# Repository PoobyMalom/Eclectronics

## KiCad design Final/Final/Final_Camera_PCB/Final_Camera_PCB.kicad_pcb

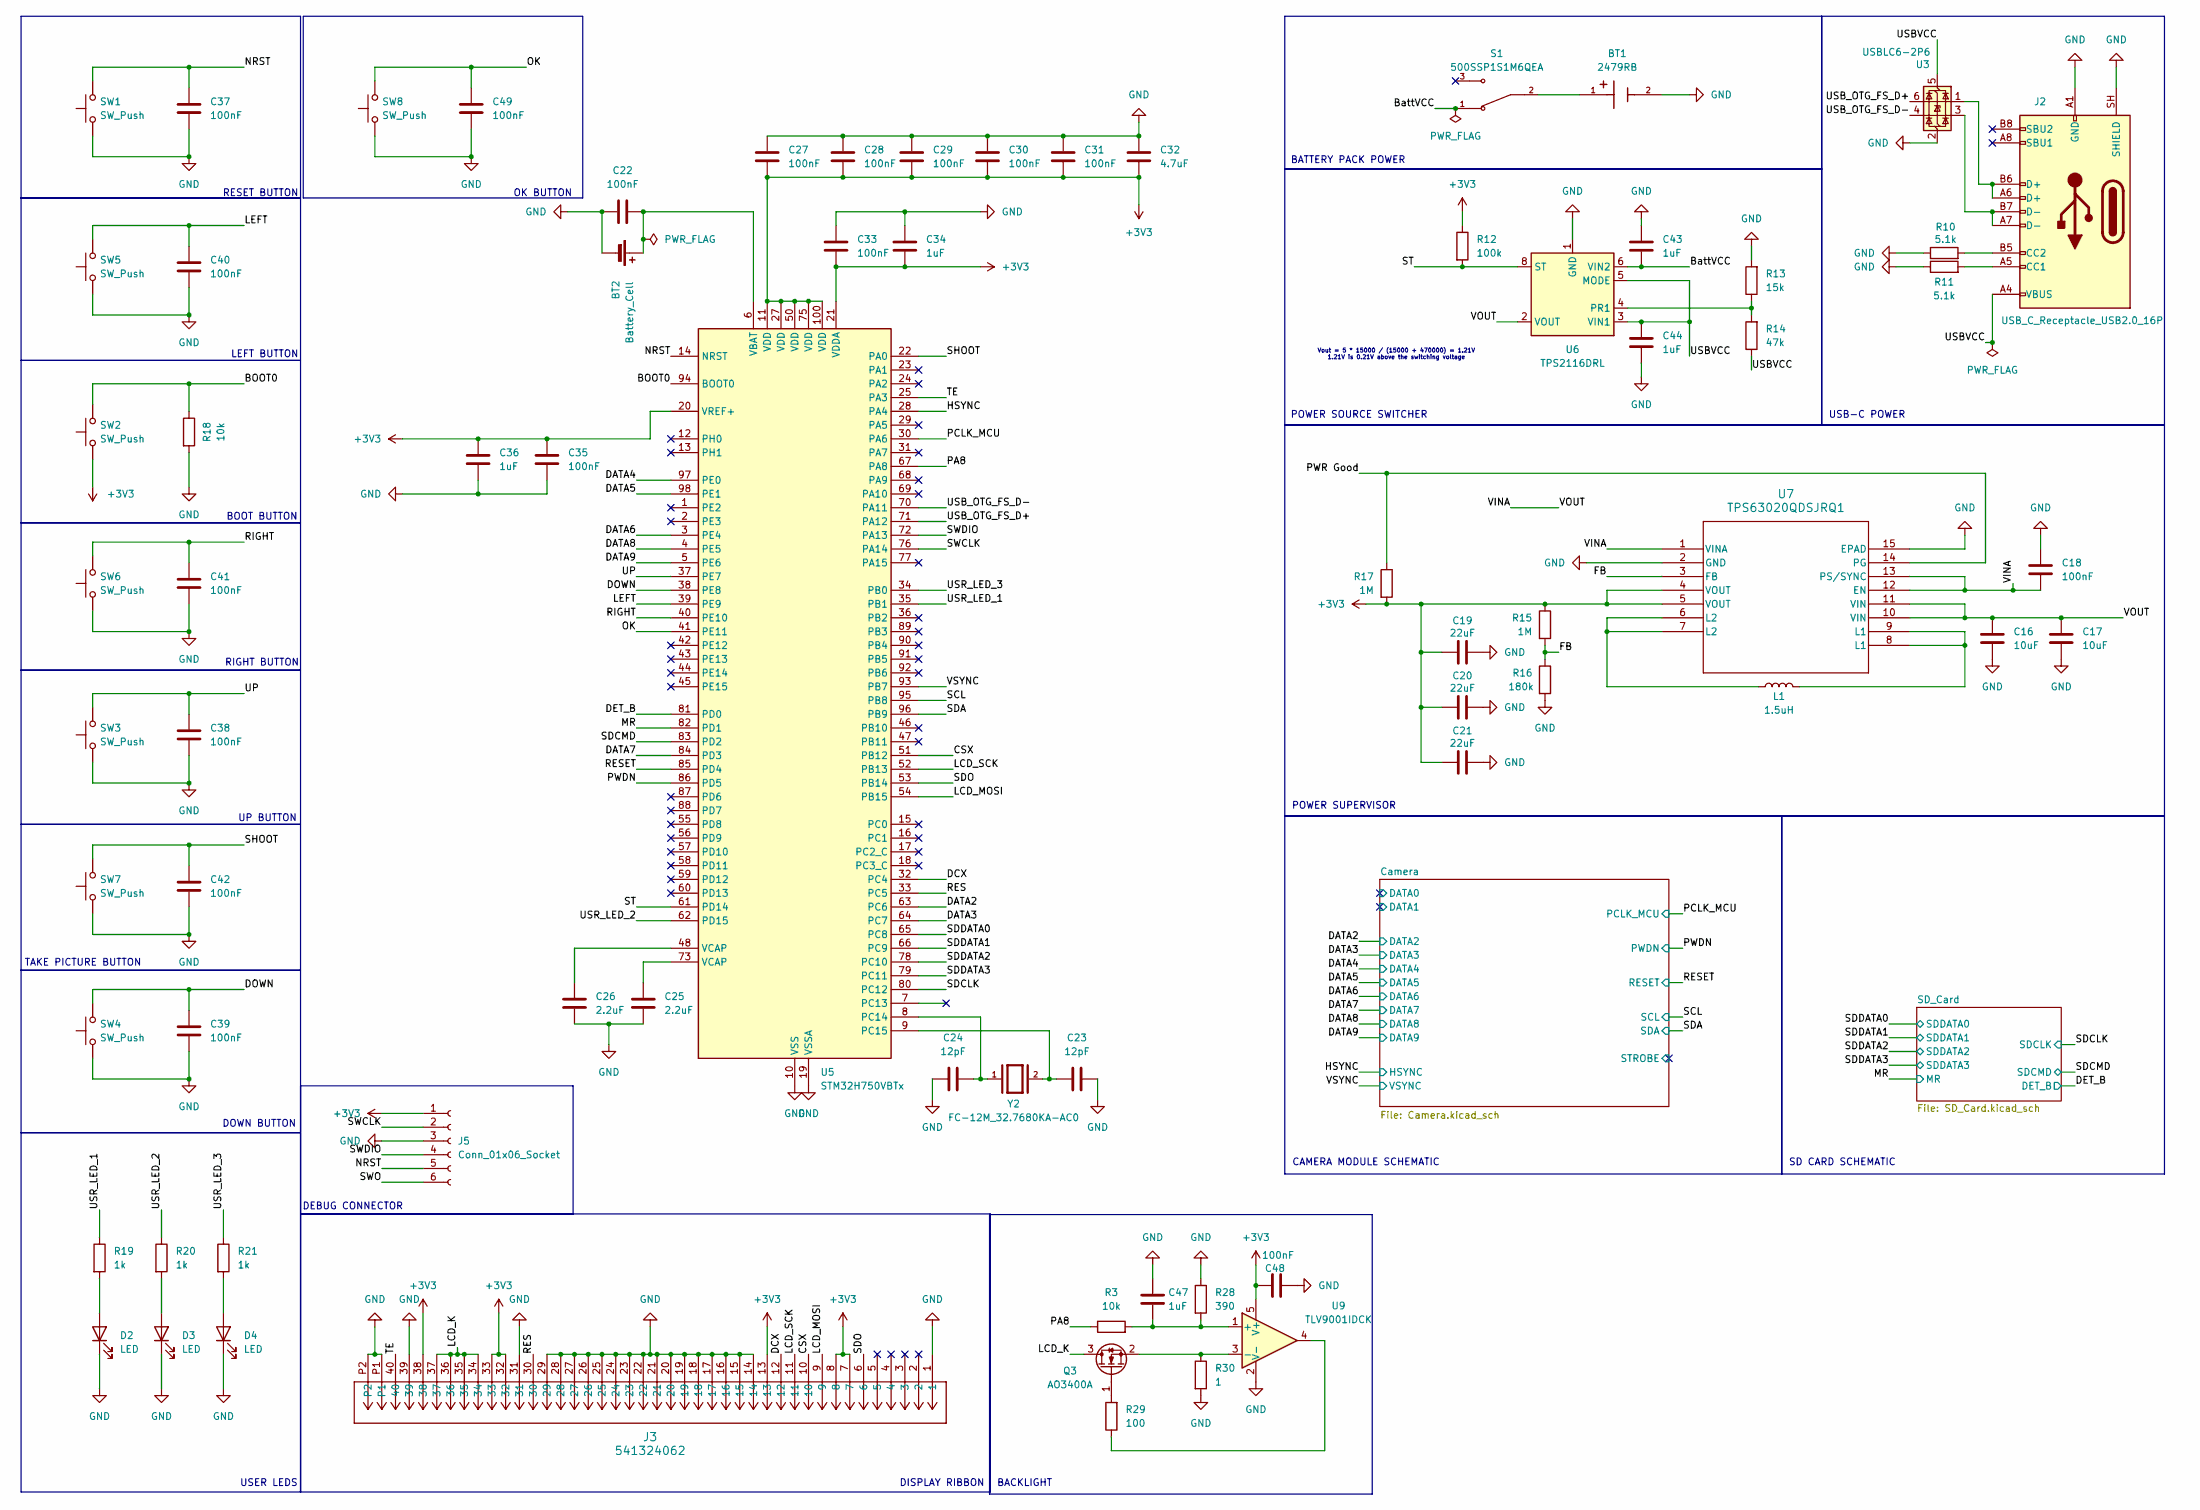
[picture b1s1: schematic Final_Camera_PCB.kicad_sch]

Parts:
BT1: 2479RB; 2479PCB_37P49X52P63_KEY; PARTREV E; DigiKey_Part_Number 36-2479RB-ND
BT2: Battery_Cell; BatteryHolder_Keystone_1060_1x2032
C16, C17: 10uF; C_0805_2012Metric
C18, C22, C27, C28, C29, C30, C31, C33, C35, C37, C38, C39, C40, C41, C42, C48, C49: 100nF; C_0402_1005Metric
C19, C20, C21: 22uF; C_1206_3216Metric
C23, C24: 12pF; C_0402_1005Metric
C25, C26: 2.2uF; C_0603_1608Metric
C32: 4.7uF; C_0603_1608Metric
C34, C36, C43, C44, C47: 1uF; C_0603_1608Metric
D2, D3, D4: LED; LED_0603_1608Metric
J2: USB_C_Receptacle_USB2.0_16P; USB_C_Receptacle_GCT_USB4105-xx-A_16P_TopMnt_Horizontal
J3: 541324062; CON_541324062_MOL
J5: Conn_01x06_Socket; PinHeader_1x06_P2.54mm_Vertical
L1: 1.5uH; L_1008_2520Metric
Q3: AO3400A; SOT-23
R3, R18: 10k; R_0402_1005Metric
R10, R11: 5.1k; R_0402_1005Metric
R12: 100k; R_0402_1005Metric
R13: 15k; R_0402_1005Metric
R14: 47k; R_0402_1005Metric
R15, R17: 1M; R_0402_1005Metric
R16: 180k; R_0402_1005Metric
R19, R20, R21: 1k; R_0402_1005Metric
R28: 390; R_0402_1005Metric
R29: 100; R_0402_1005Metric
R30: 1; R_0603_1608Metric
S1: 500SSP1S1M6QEA; SW_500SSP1S1M6QEA; PARTREV D
SW1, SW2, SW3, SW4, SW5, SW6, SW7, SW8: SW_Push; SW_SPST_B3U-1000P
U3: USBLC6-2P6; SOT-666
U5: STM32H750VBTx; LQFP-100_14x14mm_P0.5mm
U6: TPS2116DRL; SOT-583-8
U7: TPS63020QDSJRQ1; DSJ14_2P85X1P58
U9: TLV9001IDCK; SOT-353_SC-70-5
Y2: FC-12M_32.7680KA-AC0; XTAL_FC-12M_32.7680KA-AC0; MPN FC-12M 32.7680KA-AC0

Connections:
+3V3: C19.2, C20.2, C21.2, C27.2, C28.2, C29.2, C30.2, C31.2, C32.2, C33.2, C34.2, C35.2, C36.2, C48.1, J3.7, J3.8, J3.13, J3.32, J3.33, J3.38, J5.1, R12.1, R15.1, R17.2, SW2.1, U5.11 (VDD), U5.20 (VREF+), U5.21 (VDDA), U5.27 (VDD), U5.50 (VDD), U5.75 (VDD), U5.100 (VDD), U7.4 (VOUT), U7.5 (VOUT), U9.5 (V+); also elsewhere on the board
/BOOT0: R18.1, SW2.2, U5.94 (BOOT0)
/BattVCC: C43.2, S1.1, U6.6 (VIN2)
/CSX: J3.10, U5.51 (PB12)
/DATA2: U5.63 (PC6); also elsewhere on the board
/DATA3: U5.64 (PC7); also elsewhere on the board
/DATA4: U5.97 (PE0); also elsewhere on the board
/DATA5: U5.98 (PE1); also elsewhere on the board
/DATA6: U5.3 (PE4); also elsewhere on the board
/DATA7: U5.84 (PD3); also elsewhere on the board
/DATA8: U5.4 (PE5); also elsewhere on the board
/DATA9: U5.5 (PE6); also elsewhere on the board
/DCX: J3.12, U5.32 (PC4)
/DET_B: U5.81 (PD0); also elsewhere on the board
/DOWN: C39.1, SW4.2, U5.38 (PE8)
/FB: R15.2, R16.1, U7.3 (FB)
/HSYNC: U5.28 (PA4); also elsewhere on the board
/LCD_K: J3.34, J3.35, J3.36, J3.37, Q3.3 (D)
/LCD_MOSI: J3.9, U5.54 (PB15)
/LCD_SCK: J3.11, U5.52 (PB13)
/LEFT: C40.1, SW5.2, U5.39 (PE9)
/MR: U5.82 (PD1); also elsewhere on the board
/NRST: C37.1, J5.5, SW1.2, U5.14 (NRST)
/OK: C49.1, SW8.2, U5.41 (PE11)
/PA8: R3.1, U5.67 (PA8)
/PCLK_MCU: U5.30 (PA6); also elsewhere on the board
/PWDN: U5.86 (PD5); also elsewhere on the board
/PWR Good: R17.1, U7.14 (PG)
/RES: J3.30, U5.33 (PC5)
/RESET: U5.85 (PD4); also elsewhere on the board
/RIGHT: C41.1, SW6.2, U5.40 (PE10)
/SCL: U5.95 (PB8); also elsewhere on the board
/SDA: U5.96 (PB9); also elsewhere on the board
/SDCLK: U5.80 (PC12); also elsewhere on the board
/SDCMD: U5.83 (PD2); also elsewhere on the board
/SDDATA0: U5.65 (PC8); also elsewhere on the board
/SDDATA1: U5.66 (PC9); also elsewhere on the board
/SDDATA2: U5.78 (PC10); also elsewhere on the board
/SDDATA3: U5.79 (PC11); also elsewhere on the board
/SDO: J3.6, U5.53 (PB14)
/SHOOT: C42.1, SW7.2, U5.22 (PA0)
/ST: R12.2, U5.61 (PD14), U6.8 (ST)
/SWCLK: J5.2, U5.76 (PA14)
/SWDIO: J5.4, U5.72 (PA13)
/SWO: J5.6
/TE: J3.40, U5.25 (PA3)
/UP: C38.1, SW3.2, U5.37 (PE7)
/USBVCC: C44.1, J2.A4 (VBUS), J2.A9 (VBUS), J2.B4 (VBUS), J2.B9 (VBUS), R14.1, U3.5 (VBUS), U6.3 (VIN1), U6.5 (MODE)
/USB_OTG_FS_D+: U3.6 (I/O1), U5.71 (PA12)
/USB_OTG_FS_D-: U3.4 (I/O2), U5.70 (PA11)
/USR_LED_1: R19.1, U5.35 (PB1)
/USR_LED_2: R20.1, U5.62 (PD15)
/USR_LED_3: R21.1, U5.34 (PB0)
/VINA: C16.1, C17.1, C18.1, U6.2 (VOUT), U6.7 (VOUT), U7.1 (VINA), U7.10 (VIN), U7.11 (VIN), U7.12 (EN), U7.13 (PS/SYNC)
/VSYNC: U5.93 (PB7); also elsewhere on the board
GND: BT1.2, BT2.2 (-), C16.2, C17.2, C18.2, C19.1, C20.1, C21.1, C22.2, C23.1, C24.1, C25.2, C26.2, C27.1, C28.1, C29.1, C30.1, C31.1, C32.1, C33.1, C34.1, C35.1, C36.1, C37.2, C38.2, C39.2, C40.2, C41.2, C42.2, C43.1, C44.2, C47.1, C48.2, C49.2, D2.1 (K), D3.1 (K), D4.1 (K), J2.A1 (GND), J2.A12 (GND), J2.B1 (GND), J2.B12 (GND), J2.SH (SHIELD), J3.1, J3.14, J3.15, J3.16, J3.17, J3.18, J3.19, J3.20, J3.21, J3.22, J3.23, J3.24, J3.25, J3.26, J3.27, J3.28, J3.29, J3.31, J3.39, J3.P1, J3.P2, J5.3, R10.1, R11.1, R13.2, R16.2, R18.2, R28.1, R30.2, SW1.1, SW3.1, SW4.1, SW5.1, SW6.1, SW7.1, SW8.1, U3.2 (GND), U5.10 (VSS), U5.19 (VSSA), U5.26 (VSS), U5.49 (VSS), U5.74 (VSS), U5.99 (VSS), U6.1 (GND), U7.2 (GND), U7.15 (EPAD), U9.2 (V-); also elsewhere on the board
unnamed: BT1.1, S1.2
unnamed: BT2.1 (+), C22.1, U5.6 (VBAT)
unnamed: C25.1, U5.73 (VCAP)
unnamed: C26.1, U5.48 (VCAP)
unnamed: D2.2 (A), R19.2
unnamed: D3.2 (A), R20.2
unnamed: D4.2 (A), R21.2
unnamed: J2.A5 (CC1), R11.2
unnamed: J2.B5 (CC2), R10.2
unnamed: J2.A6 (D+), J2.B6 (D+), U3.1 (I/O1)
unnamed: J2.A7 (D-), J2.B7 (D-), U3.3 (I/O2)
unnamed: L1.1, U7.6 (L2), U7.7 (L2)
unnamed: L1.2, U7.8 (L1), U7.9 (L1)
unnamed: Q3.1 (G), R29.2
unnamed: Q3.2 (S), R30.1, U9.3 (-)
unnamed: R29.1, U9.4
unnamed: C24.2, U5.8 (PC14), Y2.1
unnamed: C23.2, U5.9 (PC15), Y2.2
unnamed: R13.1, R14.2, U6.4 (PR1)
unnamed: C47.2, R3.2, R28.2, U9.1 (+)

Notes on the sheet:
BOOT BUTTON
USER LEDS
DOWN BUTTON
SD CARD SCHEMATIC
OK BUTTON
RIGHT BUTTON
USB-C POWER
Vout = 5 * 15000 / (15000 + 470000) = 1.21V 1.21V is 0.21V above the switching voltage
LEFT BUTTON
DISPLAY RIBBON
UP BUTTON
RESET BUTTON
BATTERY PACK POWER
TAKE PICTURE BUTTON
POWER SUPERVISOR
CAMERA MODULE SCHEMATIC
DEBUG CONNECTOR
POWER SOURCE SWITCHER
BACKLIGHT

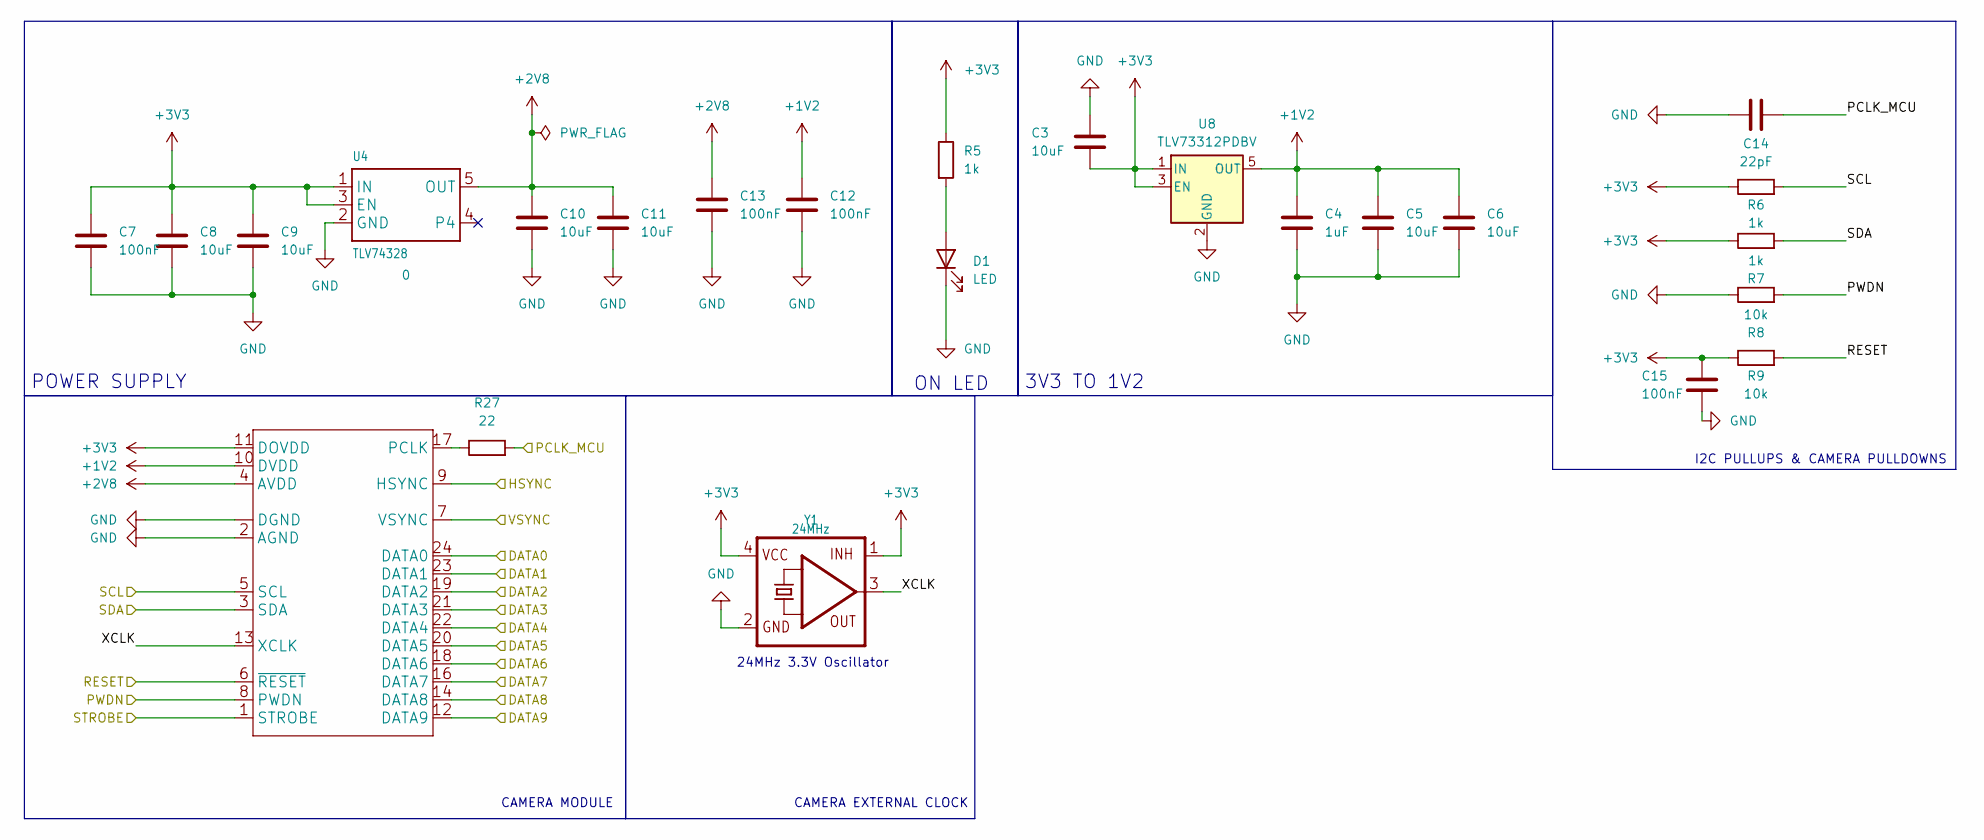
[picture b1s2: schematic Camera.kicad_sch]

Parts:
C3, C5, C6, C8, C9, C10, C11: 10uF; C_0805_2012Metric
C4: 1uF; C_0603_1608Metric
C7, C12, C13, C15: 100nF; C_0402_1005Metric
C14: 22pF; C_0402_1005Metric
D1: LED; LED_0603_1608Metric
R5, R6, R7: 1k; R_0402_1005Metric
R8, R9: 10k; R_0402_1005Metric
R27: 22; R_0402_1005Metric
U4: TLV74328; DBV0005A_N; JLC_ROTATION 270
U8: TLV73312PDBV; SOT-23-5
X1: OV2640FSL
Y1: 24MHz; Oscillator_SMD_Abracon_ASE-4Pin_3.2x2.5mm_HandSoldering

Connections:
+1V2: C4.1, C5.1, C6.1, C12.1, U8.5 (OUT), X1.10 (DVDD)
+2V8: C10.1, C11.1, C13.1, U4.5 (OUT), X1.4 (AVDD)
+3V3: C3.2, C7.1, C8.1, C9.1, C15.2, R5.1, R6.1, R7.1, R9.1, U4.1 (IN), U4.3 (EN), U8.1 (IN), U8.3 (EN), X1.11 (DOVDD), Y1.1 (INH), Y1.4 (VCC); also elsewhere on the board
/Camera/DATA0: X1.24 (DATA0)
/Camera/DATA1: X1.23 (DATA1)
/Camera/STROBE: X1.1 (STROBE)
/Camera/XCLK: X1.13 (XCLK), Y1.3 (OUT)
/DATA2: X1.19 (DATA2); also elsewhere on the board
/DATA3: X1.21 (DATA3); also elsewhere on the board
/DATA4: X1.22 (DATA4); also elsewhere on the board
/DATA5: X1.20 (DATA5); also elsewhere on the board
/DATA6: X1.18 (DATA6); also elsewhere on the board
/DATA7: X1.16 (DATA7); also elsewhere on the board
/DATA8: X1.14 (DATA8); also elsewhere on the board
/DATA9: X1.12 (DATA9); also elsewhere on the board
/HSYNC: X1.9 (HSYNC); also elsewhere on the board
/PCLK_MCU: C14.1, R27.2; also elsewhere on the board
/PWDN: R8.2, X1.8 (PWDN); also elsewhere on the board
/RESET: R9.2, X1.6 (~RESET); also elsewhere on the board
/SCL: R6.2, X1.5 (SCL); also elsewhere on the board
/SDA: R7.2, X1.3 (SDA); also elsewhere on the board
/VSYNC: X1.7 (VSYNC); also elsewhere on the board
GND: C3.1, C4.2, C5.2, C6.2, C7.2, C8.2, C9.2, C10.2, C11.2, C12.2, C13.2, C14.2, C15.1, D1.1 (K), R8.1, U4.2 (GND), U8.2 (GND), X1.2 (AGND), X1.15 (DGND), X1.SPRT1 (DGND), X1.SPRT2 (DGND), Y1.2 (GND); also elsewhere on the board
unnamed: D1.2 (A), R5.2
unnamed: R27.1, X1.17 (PCLK)

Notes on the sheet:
24MHz 3.3V Oscillator
3V3 TO 1V2
I2C PULLUPS & CAMERA PULLDOWNS
CAMERA EXTERNAL CLOCK
CAMERA MODULE
POWER SUPPLY
ON LED

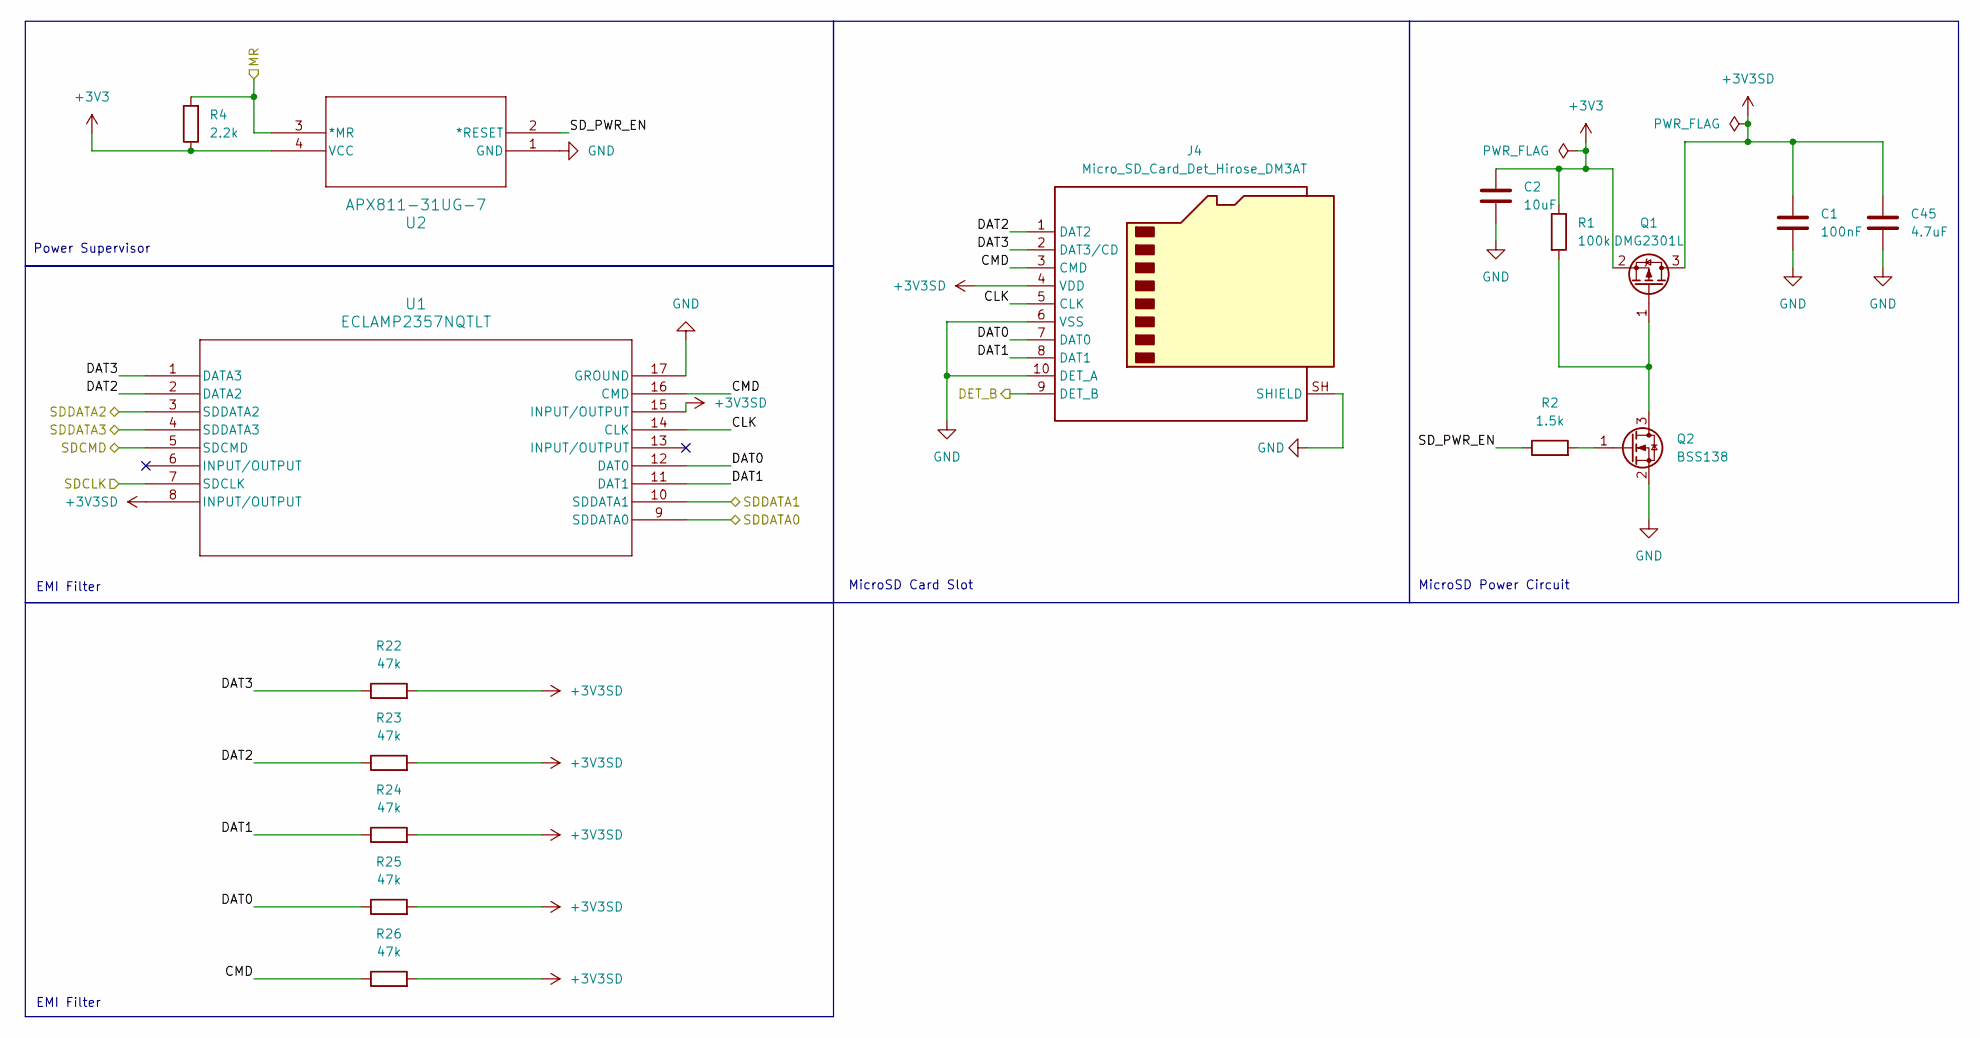
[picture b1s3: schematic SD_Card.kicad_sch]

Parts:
C1: 100nF; C_0402_1005Metric
C2: 10uF; C_0805_2012Metric
C45: 4.7uF; C_0603_1608Metric
J4: Micro_SD_Card_Det_Hirose_DM3AT; microSD_HC_Hirose_DM3AT-SF-PEJM5
Q1: DMG2301L; SOT-23
Q2: BSS138; SOT-23
R1: 100k; R_0402_1005Metric
R2: 1.5k; R_0402_1005Metric
R4: 2.2k; R_0402_1005Metric
R22, R23, R24, R25, R26: 47k; R_0402_1005Metric
U1: ECLAMP2357NQTLT; UQFN-16-1EP_3x3mm_P0.5mm_EP1.75x1.75mm
U2: APX811-31UG-7; APX811-31UG-7_DIO

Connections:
+3V3: C2.1, Q1.2 (S), R1.1, R4.1, U2.4 (VCC); also elsewhere on the board
+3V3SD: C1.1, C45.1, J4.4 (VDD), Q1.3 (D), R22.2, R23.2, R24.2, R25.2, R26.2, U1.8 (INPUT/OUTPUT), U1.15 (INPUT/OUTPUT)
/DET_B: J4.9 (DET_B); also elsewhere on the board
/MR: R4.2, U2.3 (*MR); also elsewhere on the board
/SDCLK: U1.7 (SDCLK); also elsewhere on the board
/SDCMD: U1.5 (SDCMD); also elsewhere on the board
/SDDATA0: U1.9 (SDDATA0); also elsewhere on the board
/SDDATA1: U1.10 (SDDATA1); also elsewhere on the board
/SDDATA2: U1.3 (SDDATA2); also elsewhere on the board
/SDDATA3: U1.4 (SDDATA3); also elsewhere on the board
/SD_Card/CLK: J4.5 (CLK), U1.14 (CLK)
/SD_Card/CMD: J4.3 (CMD), R26.1, U1.16 (CMD)
/SD_Card/DAT0: J4.7 (DAT0), R25.1, U1.12 (DAT0)
/SD_Card/DAT1: J4.8 (DAT1), R24.1, U1.11 (DAT1)
/SD_Card/DAT2: J4.1 (DAT2), R23.1, U1.2 (DATA2)
/SD_Card/DAT3: J4.2 (DAT3/CD), R22.1, U1.1 (DATA3)
/SD_Card/SD_PWR_EN: R2.1, U2.2 (*RESET)
GND: C1.2, C2.2, C45.2, J4.6 (VSS), J4.10 (DET_A), J4.SH (SHIELD), Q2.2 (S), U1.17 (GROUND), U2.1 (GND); also elsewhere on the board
unnamed: Q1.1 (G), Q2.3 (D), R1.2
unnamed: Q2.1 (G), R2.2

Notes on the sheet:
Power Supervisor
EMI Filter
MicroSD Power Circuit
MicroSD Card Slot

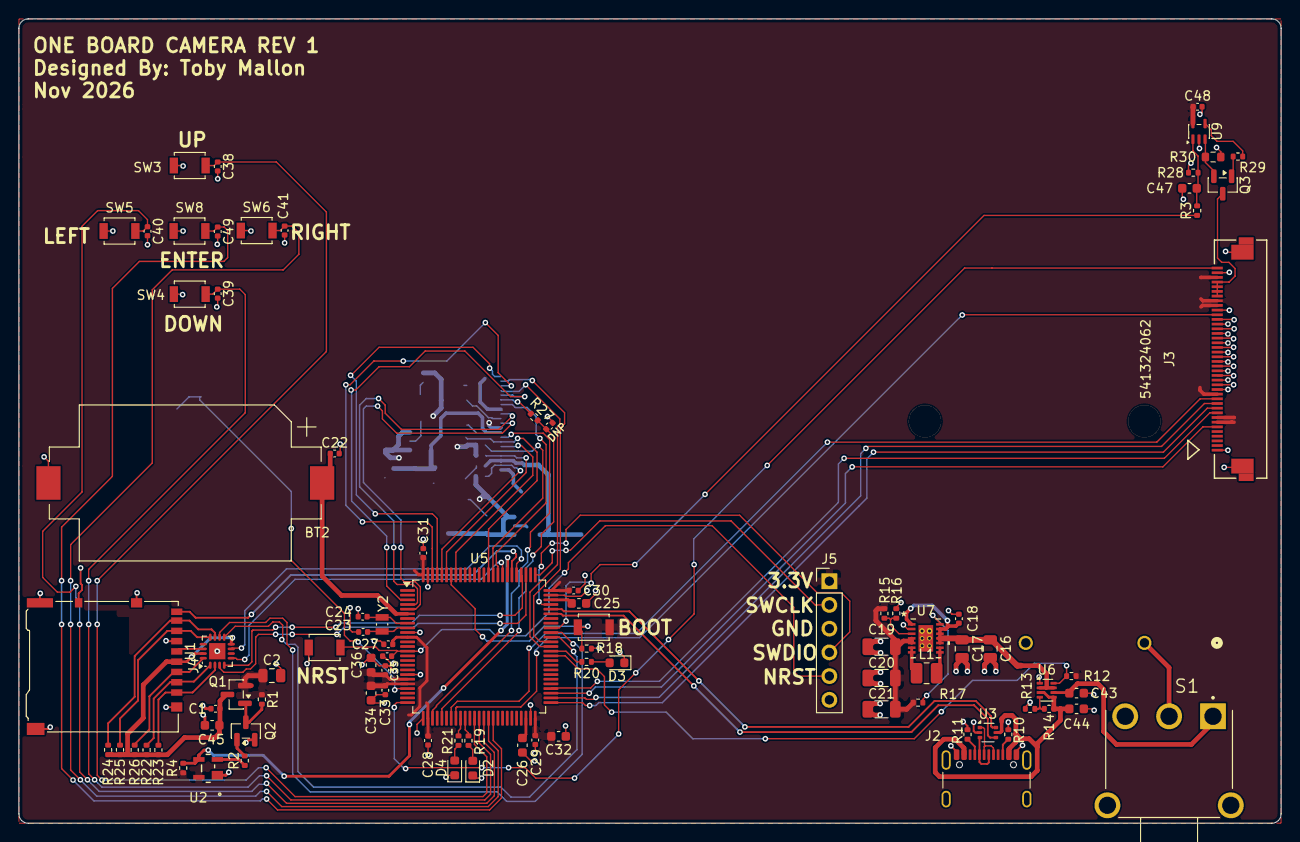
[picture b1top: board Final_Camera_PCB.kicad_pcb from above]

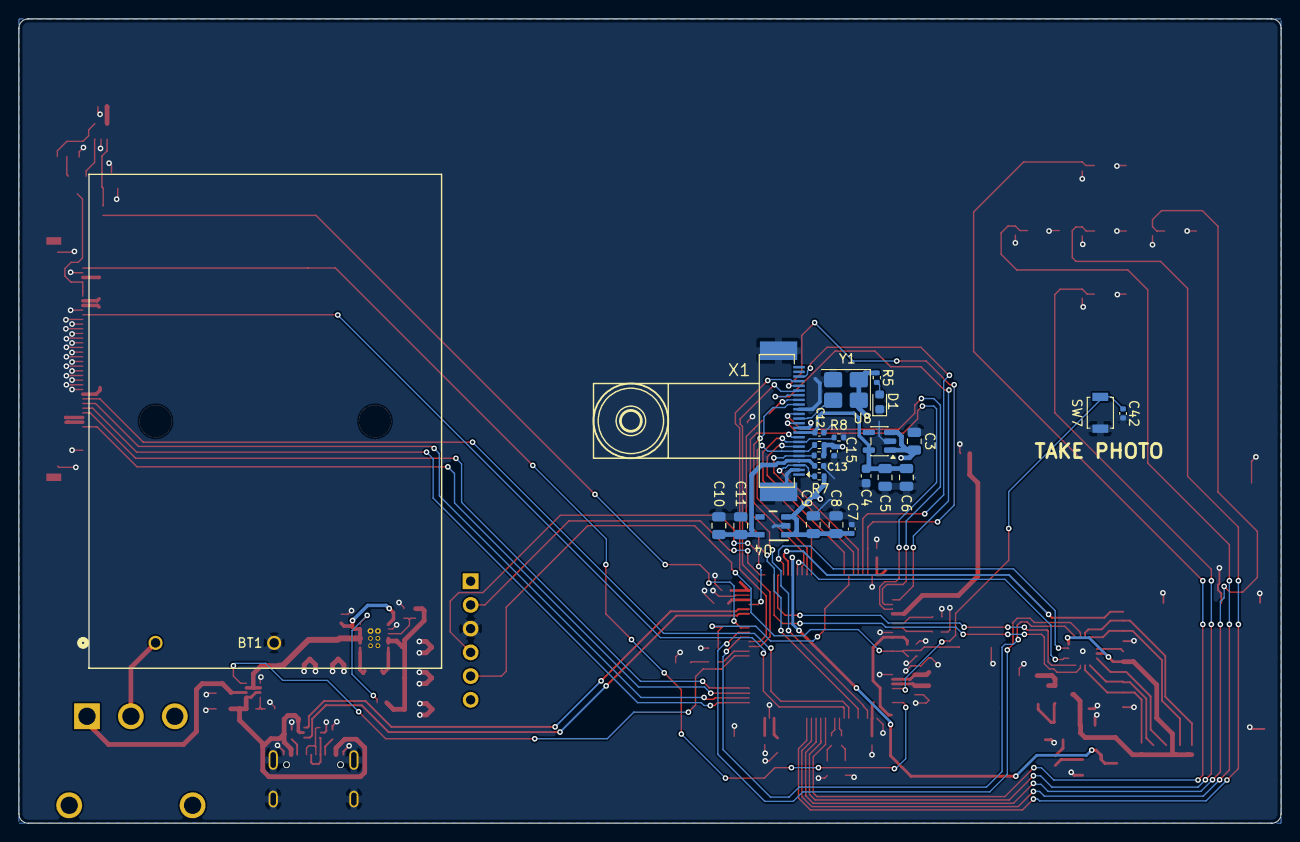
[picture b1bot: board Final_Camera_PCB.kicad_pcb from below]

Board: 2 copper layers, 135.1 x 86.1 mm, 113 parts (25 on the bottom side), 90 nets.

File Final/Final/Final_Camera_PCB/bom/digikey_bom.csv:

Quantity,Manufacturer Part Number,Manufacturer,Customer Reference,Description,Per Board,Link
2,STM32H750VBT6,STMicroelectronics,U5,"MCU, LQFP-100",1,https://www.digikey.com/en/products/detail/stmicroelectronic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
3,TPS63020QDSJRQ1,Texas Instruments,U7,"Buck-boost 3.3V, VSON-14 (+1 spare)",1,https://www.digikey.com/en/products/detail/texas-instruments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
3,TPS2116DRLR,Texas Instruments,U6,"Power mux, SOT-583 (+1 spare)",1,https://www.digikey.com/en/products/result?keywords=TPS2116DRLR
2,TLV74328PDBVR,Texas Instruments,U4,"LDO 2.8V, SOT-23-5",1,https://www.digikey.com/en/products/detail/texas-instruments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
2,TLV73312PDBVR,Texas Instruments,U8,"LDO 1.2V, SOT-23-5",1,https://www.digikey.com/en/products/result?keywords=TLV73312PDBVR
2,TLV9001IDCKR,Texas Instruments,U9,"Op-amp (backlight), SC-70-5",1,https://www.digikey.com/en/products/result?keywords=TLV9001IDCKR
3,ECLAMP2357NQTCT,Semtech,U1,"SD EMI/ESD filter, UQFN-16 (+1 spare)",1,https://www.digikey.com/en/products/result?keywords=ECLAMP2357NQTCT
2,APX811-31UG-7,Diodes Inc,U2,Reset supervisor,1,https://www.digikey.com/en/products/result?keywords=APX811-31UG-7
3,USBLC6-2P6,STMicroelectronics,U3,"USB ESD, SOT-666 (+1 spare)",1,https://www.digikey.com/en/products/result?keywords=USBLC6-2P6
5,DMG2301L-7,Diodes Inc,Q1,"P-MOSFET, SOT-23",1,https://www.digikey.com/en/products/result?keywords=DMG2301L-7
5,BSS138,onsemi,Q2,"N-MOSFET, SOT-23",1,https://www.digikey.com/en/products/result?keywords=BSS138
5,AO3400A,Alpha & Omega,Q3,"N-MOSFET, SOT-23 (alt: DMN3404L-7)",1,https://www.digikey.com/en/products/result?keywords=AO3400A
2,ECS-3225MV-240-BN-TR,ECS Inc,Y1,"24 MHz oscillator, 3.2x2.5",1,https://www.digikey.com/en/products/detail/ecs-inc/ECS-3225M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
3,FC-12M 32.7680KA-AC0,Epson,Y2,"32.768 kHz crystal, 2.0x1.2, 9 pF (+1 spare)",1,https://www.digikey.com/en/products/result?keywords=FC-12M%2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
2,TFM252012ALMA1R5MTAA,TDK,L1,"1.5 uH 3.3 A Isat, 2520",1,https://www.digikey.com/en/products/detail/tdk/TFM252012ALMA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
2,NHD-2.8-240320AF-CSXP-F,Newhaven Display,LCD,2.8in TFT display (plugs into J3),1,https://www.digikey.com/en/products/detail/newhaven-display-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
2,0541324062,Molex,J3,40-pin 0.5mm FFC connector,1,https://www.digikey.com/en/products/result?keywords=0541324062
2,DM3AT-SF-PEJM5,Hirose,J4,microSD socket,1,https://www.digikey.com/en/products/detail/hirose-electric-c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
2,USB4105-GF-A,GCT,J2,"USB-C receptacle, USB 2.0",1,https://www.digikey.com/en/products/result?keywords=USB4105-GF-A
2,PRPC006SAAN-RC,Sullins,J5,1x6 2.54mm male header (SWD),1,https://www.digikey.com/en/products/result?keywords=PRPC006SAAN-RC
2,500SSP1S1M6QEA,E-Switch,S1,Slide power switch,1,https://www.digikey.com/en/products/result?keywords=500SSP1S1M6QEA
20,B3U-1000P,Omron,SW1-SW8,Tactile switch SMD (+4 spare),8,https://www.digikey.com/en/products/result?keywords=B3U-1000P
2,2479RB,Keystone,BT1,3xAAA holder,1,https://www.digikey.com/en/products/detail/keystone-electron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
2,1060,Keystone,BT2,CR2032 holder,1,https://www.digikey.com/en/products/detail/keystone-electron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
5,LTST-C191KGKT,Lite-On,D1,Green LED 0603 (power),1,https://www.digikey.com/en/products/result?keywords=LTST-C191KGKT
10,LTST-C191KRKT,Lite-On,D2-D4,Red LED 0603 (user),3,https://www.digikey.com/en/products/result?keywords=LTST-C191KRKT
50,CL05B104KO5NNNC,Samsung,100nF x22,100nF 16V X7R 0402,22,https://www.digikey.com/en/products/result?keywords=CL05B104KO5NNNC
25,CL21A106KOQNNNE,Samsung,"C2,C3,C5,C6,C8-C11,C16,C17",10uF 16V X5R 0805,10,https://www.digikey.com/en/products/result?keywords=CL21A106KOQNNNE
15,CL10B105KA8NNNC,Samsung,"C4,C34,C36,C43,C44,C47",1uF 25V X7R 0603,6,https://www.digikey.com/en/products/result?keywords=CL10B105KA8NNNC
10,CL31A226KAHNNNE,Samsung,C19-C21,22uF 25V X5R 1206,3,https://www.digikey.com/en/products/result?keywords=CL31A226KAHNNNE
10,CL10A225KO8NNNC,Samsung,"C25,C26",2.2uF 16V X5R 0603 (VCAP),2,https://www.digikey.com/en/products/result?keywords=CL10A225KO8NNNC
10,GRM188R61A475KE15D,Murata,"C32,C45",4.7uF 10V X5R 0603,2,https://www.digikey.com/en/products/result?keywords=GRM188R6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
10,CL05C120JB5NNNC,Samsung,"C23,C24",12pF 50V C0G 0402,2,https://www.digikey.com/en/products/result?keywords=CL05C120JB5NNNC
10,CL05C220JB5NNNC,Samsung,C14,22pF 50V C0G 0402 (optional/DNP),1,https://www.digikey.com/en/products/result?keywords=CL05C220JB5NNNC
10,RC0402FR-07100KL,Yageo,"R1,R12",100k 1% 0402,2,https://www.digikey.com/en/products/result?keywords=RC0402FR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
10,RC0402FR-071K5L,Yageo,R2,1.5k 1% 0402,1,https://www.digikey.com/en/products/result?keywords=RC0402FR-071K5L
10,RC0402FR-0710KL,Yageo,"R3,R8,R9,R18",10k 1% 0402,4,https://www.digikey.com/en/products/result?keywords=RC0402FR-0710KL
10,RC0402FR-072K2L,Yageo,R4,2.2k 1% 0402,1,https://www.digikey.com/en/products/result?keywords=RC0402FR-072K2L
15,RC0402FR-071KL,Yageo,"R5-R7,R19-R21",1k 1% 0402,6,https://www.digikey.com/en/products/result?keywords=RC0402FR-071KL
10,RC0402FR-075K1L,Yageo,"R10,R11",5.1k 1% 0402 (USB-C CC),2,https://www.digikey.com/en/products/result?keywords=RC0402FR-075K1L
10,RC0402FR-0715KL,Yageo,R13,15k 1% 0402,1,https://www.digikey.com/en/products/result?keywords=RC0402FR-0715KL
15,RC0402FR-0747KL,Yageo,"R14,R22-R26",47k 1% 0402,6,https://www.digikey.com/en/products/result?keywords=RC0402FR-0747KL
10,RC0402FR-071ML,Yageo,"R15,R17",1M 1% 0402,2,https://www.digikey.com/en/products/result?keywords=RC0402FR-071ML
10,RC0402FR-07180KL,Yageo,R16,180k 1% 0402,1,https://www.digikey.com/en/products/result?keywords=RC0402FR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
10,RC0402FR-0722RL,Yageo,R27,22R 1% 0402 (PCLK),1,https://www.digikey.com/en/products/result?keywords=RC0402FR-0722RL
10,RC0402FR-07390RL,Yageo,R28,390R 1% 0402,1,https://www.digikey.com/en/products/result?keywords=RC0402FR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
10,RC0402FR-07100RL,Yageo,R29,100R 1% 0402,1,https://www.digikey.com/en/products/result?keywords=RC0402FR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
10,RC0603FR-071RL,Yageo,R30,1R 1% 0603 (backlight sense),1,https://www.digikey.com/en/products/result?keywords=RC0603FR-071RL

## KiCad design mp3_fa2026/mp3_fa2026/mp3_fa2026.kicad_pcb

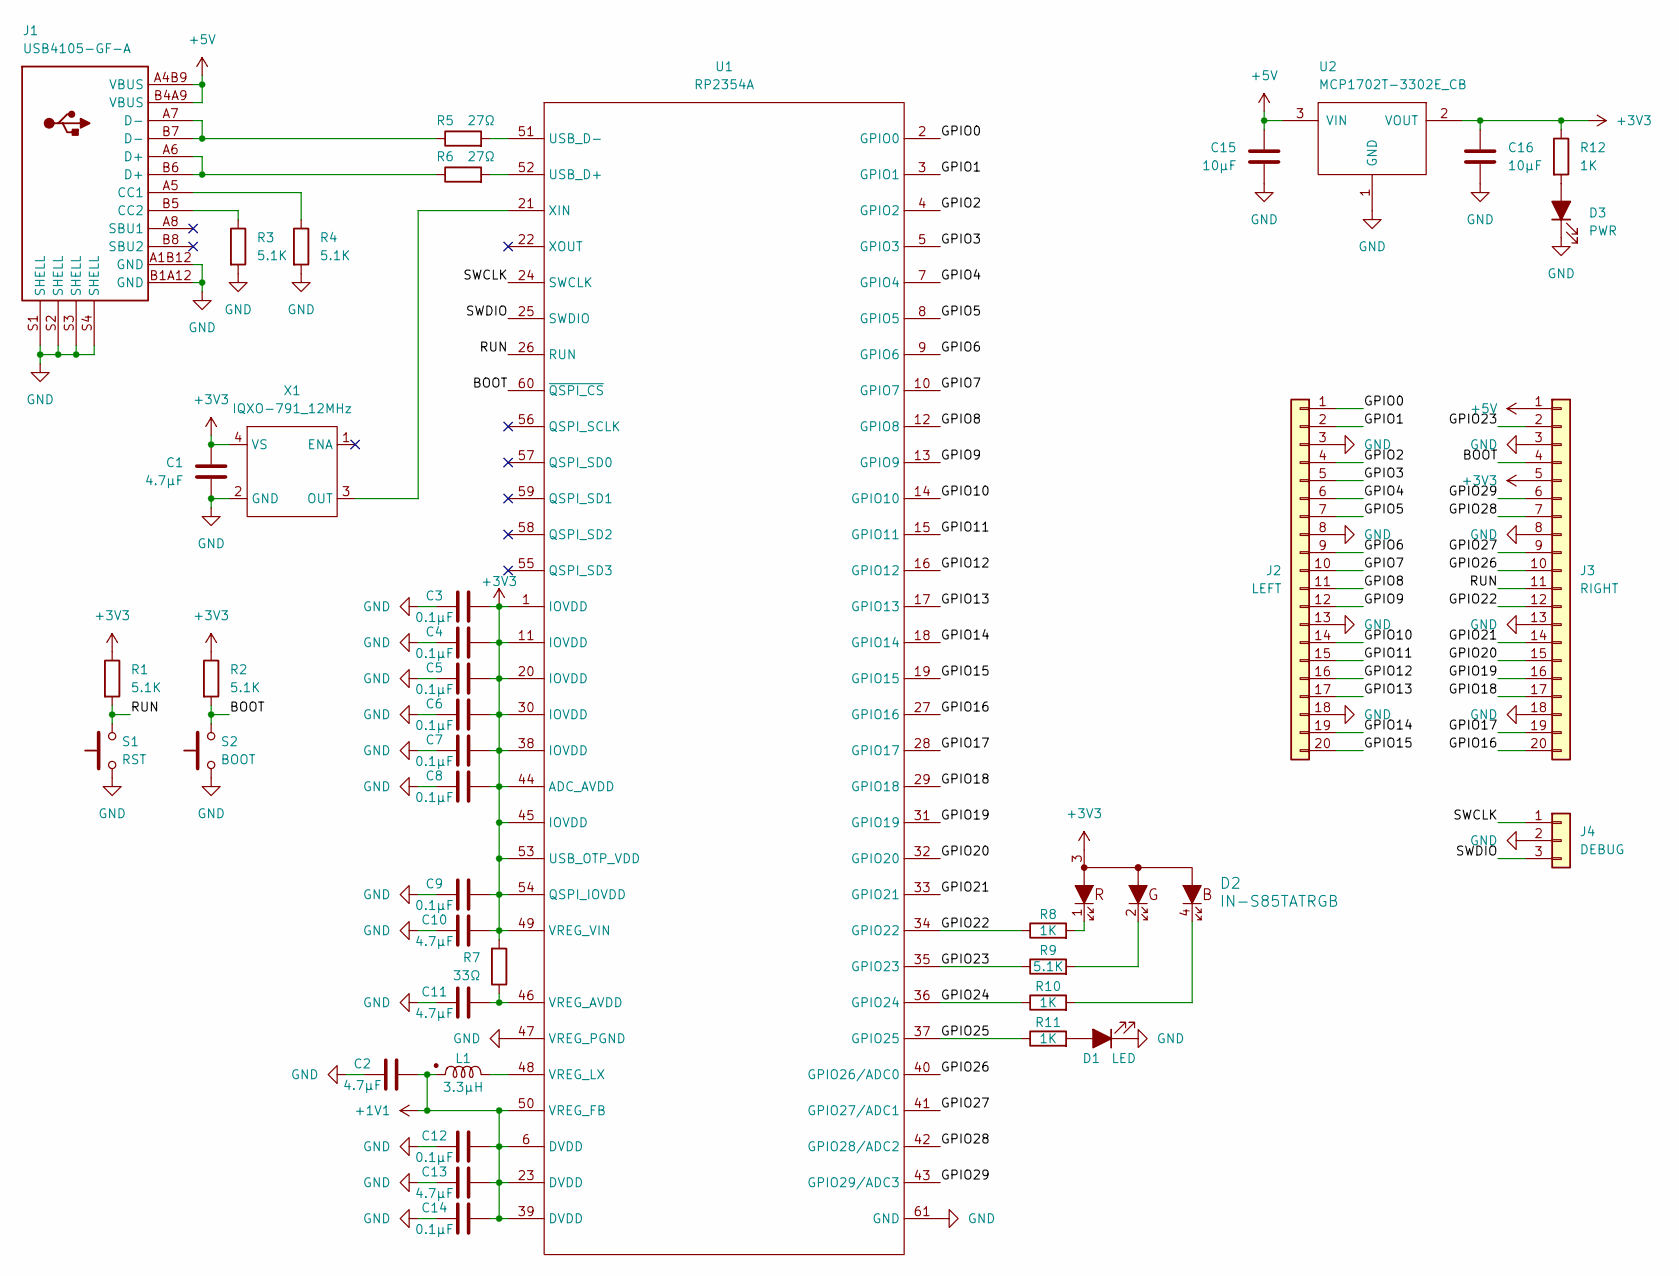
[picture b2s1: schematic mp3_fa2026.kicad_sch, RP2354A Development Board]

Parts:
C1, C2, C10, C11, C13: 4.7µF; C_0402_1005Metric
C3, C4, C5, C6, C7, C8, C9, C12, C14: 0.1µF; C_0402_1005Metric
C15, C16: 10µF; C_0603_1608Metric
D1: LED; LED_0805_2012Metric
D2: IN-S85TATRGB
D3: PWR; LED_0805_2012Metric
J1: USB4105-GF-A; USB4105-GF-A_1
J2: LEFT; PinHeader_1x20_P2.54mm_Vertical
J3: RIGHT; PinHeader_1x20_P2.54mm_Vertical
J4: DEBUG; PinHeader_1x03_P2.54mm_Vertical
L1: 3.3µH; AOTA-B201610S3R3-101-T
R1, R2, R3, R4, R9: 5.1K; R_0402_1005Metric
R5, R6: 27Ω; R_0402_1005Metric
R7: 33Ω; R_0402_1005Metric
R8, R10, R11, R12: 1K; R_0402_1005Metric
S1: RST; B3U-1000P
S2: BOOT; B3U-1000P
U1: RP2354A; RP2350A_QFN-60_EP_7.75x7.75_Pitch0.4mm
U2: MCP1702T-3302E_CB; SOT-23-3
X1: IQXO-791_12MHz; Oscillator_SMD_Abracon_ASDMB-4Pin_2.5x2.0mm

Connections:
+1V1: C2.2, C12.2, C13.2, C14.2, L1.1, U1.6 (DVDD), U1.23 (DVDD), U1.39 (DVDD), U1.50 (VREG_FB)
+3V3: C1.2, C3.2, C4.2, C5.2, C6.2, C7.2, C8.2, C9.2, C10.2, C16.1, D2.3, J3.5, R1.1, R2.1, R7.2, R12.1, U1.1 (IOVDD), U1.11 (IOVDD), U1.20 (IOVDD), U1.30 (IOVDD), U1.38 (IOVDD), U1.44 (ADC_AVDD), U1.45 (IOVDD), U1.49 (VREG_VIN), U1.53 (USB_OTP_VDD), U1.54 (QSPI_IOVDD), U2.2 (VOUT), X1.4 (VS)
+5V: C15.2, J1.A4B9 (VBUS), J1.B4A9 (VBUS), J3.1, U2.3 (VIN)
/BOOT: J3.4, R2.2, S2.2, U1.60 (~QSPI_CS)
/GPIO0: J2.1, U1.2 (GPIO0)
/GPIO1: J2.2, U1.3 (GPIO1)
/GPIO2: J2.4, U1.4 (GPIO2)
/GPIO3: J2.5, U1.5 (GPIO3)
/GPIO4: J2.6, U1.7 (GPIO4)
/GPIO5: J2.7, U1.8 (GPIO5)
/GPIO6: J2.9, U1.9 (GPIO6)
/GPIO7: J2.10, U1.10 (GPIO7)
/GPIO8: J2.11, U1.12 (GPIO8)
/GPIO9: J2.12, U1.13 (GPIO9)
/GPIO10: J2.14, U1.14 (GPIO10)
/GPIO11: J2.15, U1.15 (GPIO11)
/GPIO12: J2.16, U1.16 (GPIO12)
/GPIO13: J2.17, U1.17 (GPIO13)
/GPIO14: J2.19, U1.18 (GPIO14)
/GPIO15: J2.20, U1.19 (GPIO15)
/GPIO16: J3.20, U1.27 (GPIO16)
/GPIO17: J3.19, U1.28 (GPIO17)
/GPIO18: J3.17, U1.29 (GPIO18)
/GPIO19: J3.16, U1.31 (GPIO19)
/GPIO20: J3.15, U1.32 (GPIO20)
/GPIO21: J3.14, U1.33 (GPIO21)
/GPIO22: J3.12, R8.1, U1.34 (GPIO22)
/GPIO23: J3.2, R9.1, U1.35 (GPIO23)
/GPIO24: R10.1, U1.36 (GPIO24)
/GPIO25: R11.1, U1.37 (GPIO25)
/GPIO26: J3.10, U1.40 (GPIO26/ADC0)
/GPIO27: J3.9, U1.41 (GPIO27/ADC1)
/GPIO28: J3.7, U1.42 (GPIO28/ADC2)
/GPIO29: J3.6, U1.43 (GPIO29/ADC3)
/RUN: J3.11, R1.2, S1.2, U1.26 (RUN)
/SWCLK: J4.1, U1.24 (SWCLK)
/SWDIO: J4.3, U1.25 (SWDIO)
GND: C1.1, C2.1, C3.1, C4.1, C5.1, C6.1, C7.1, C8.1, C9.1, C10.1, C11.1, C12.1, C13.1, C14.1, C15.1, C16.2, D1.1 (K), D3.1 (K), J1.A1B12 (GND), J1.B1A12 (GND), J1.S1 (SHELL), J1.S2 (SHELL), J1.S3 (SHELL), J1.S4 (SHELL), J2.3, J2.8, J2.13, J2.18, J3.3, J3.8, J3.13, J3.18, J4.2, R3.2, R4.2, S1.1, S2.1, U1.47 (VREG_PGND), U1.61 (GND), U2.1 (GND), X1.2 (GND)
unnamed: D1.2 (A), R11.2
unnamed: D2.1, R8.2
unnamed: D2.2, R9.2
unnamed: D2.4, R10.2
unnamed: D3.2 (A), R12.2
unnamed: J1.A5 (CC1), R4.1
unnamed: J1.B5 (CC2), R3.1
unnamed: J1.A6 (D+), J1.B6 (D+), R6.1
unnamed: J1.A7 (D-), J1.B7 (D-), R5.1
unnamed: R6.2, U1.52 (USB_D+)
unnamed: R5.2, U1.51 (USB_D-)
unnamed: C11.2, R7.1, U1.46 (VREG_AVDD)
unnamed: L1.2, U1.48 (VREG_LX)
unnamed: U1.21 (XIN), X1.3 (OUT)

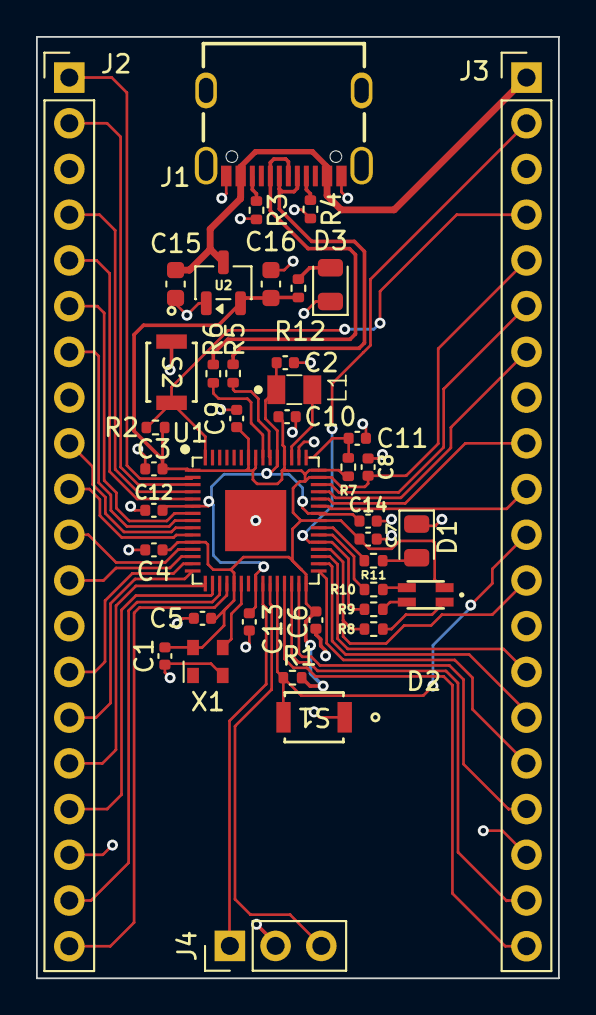
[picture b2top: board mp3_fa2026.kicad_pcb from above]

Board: 2 copper layers, 29.0 x 52.3 mm, 41 parts (0 on the bottom side), 52 nets.
